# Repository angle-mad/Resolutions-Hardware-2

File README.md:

# Sasuke Bistable Multivibrator

This PCB is a Bistable Multivibrator in the shape of Sasuke from the anime Naruto. The LEDs change sides once a push switch gets pressed. There are two push swithes and the LED changes to go to the side opposite to the pussh switch. The LEDs are supposed to represent Sasuke's sharingan eyes. I made this projet because I want to better my hardware skills and because Naruto is one of my favorite shows and it is interesting way to show a Multivibrator that works with the show. 

---
## Lapse

[Lapse Video](https://lapse.hackclub.com/timelapse/BlOlKrzwhdhR)

## Simulation

The Bistable Multivibrator has two stable states. The circuit can stay in one of the two positions. This changes when a push switch is pressed. The push switch that is under the LED that is on will switch the state and cause the opposite LED to turn on.

[Link to Demo](https://is.gd/yXgSkD)

---
## Schematic

## PCB

---

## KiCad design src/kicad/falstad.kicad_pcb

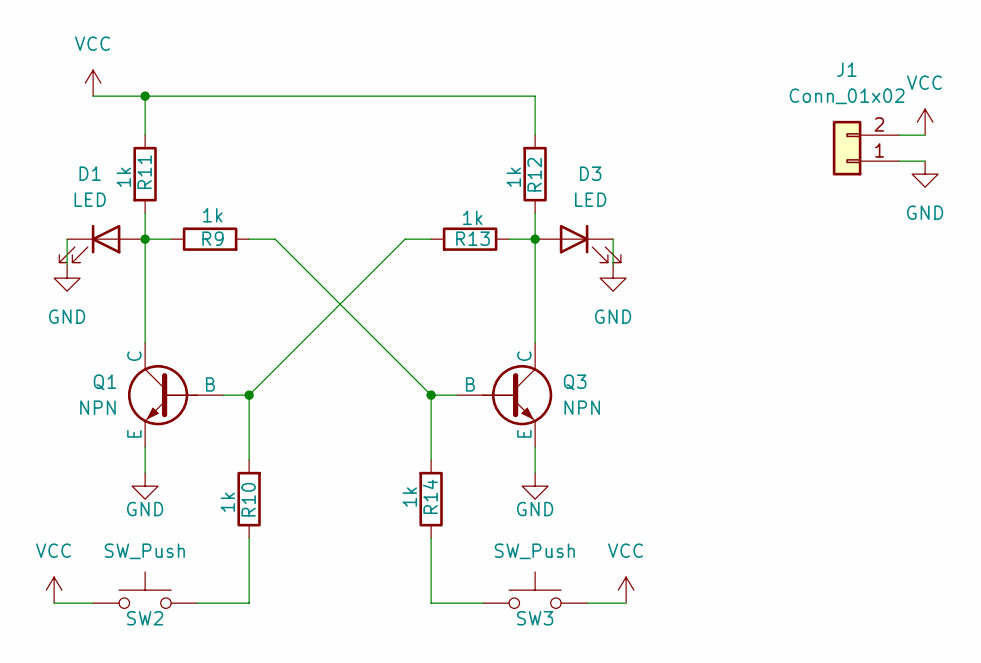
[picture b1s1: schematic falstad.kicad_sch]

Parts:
D1, D3: LED; LED_D5.0mm
J1: Conn_01x02; PinHeader_1x02_P2.54mm_Vertical
Q1, Q3: NPN; TO-92L_Inline_Wide
R9, R10, R11, R12, R13, R14: 1k; R_Axial_DIN0204_L3.6mm_D1.6mm_P7.62mm_Horizontal
SW2, SW3: SW_Push; SW_PUSH_6mm

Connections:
GND: D1.1 (K), D3.1 (K), J1.1, Q1.3 (E), Q3.3 (E)
unnamed: D1.2 (A), Q1.1 (C), R9.1, R11.2
unnamed: D3.2 (A), Q3.1 (C), R12.1, R13.1
unnamed: Q1.2 (B), R10.2, R13.2
unnamed: Q3.2 (B), R9.2, R14.2
unnamed: R10.1, SW2.2
unnamed: R14.1, SW3.2
VCC: J1.2, R11.1, R12.2, SW2.1, SW3.1

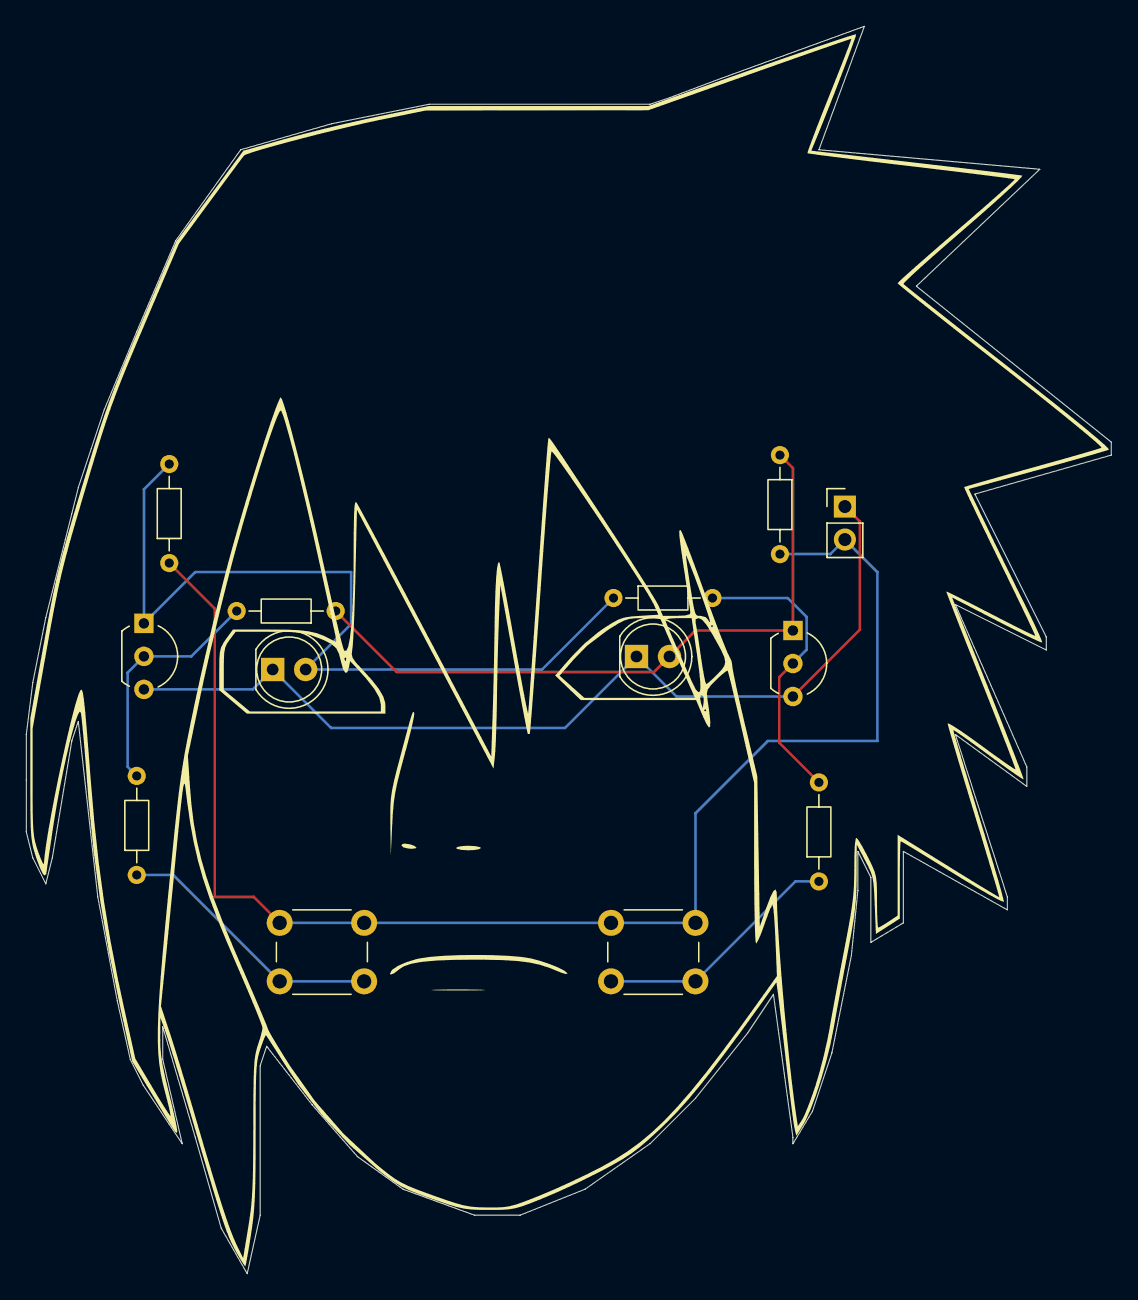
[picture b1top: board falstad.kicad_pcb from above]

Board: 2 copper layers, 83.5 x 96.0 mm, 13 parts (0 on the bottom side), 8 nets.

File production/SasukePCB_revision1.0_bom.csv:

Designator,Footprint,Quantity,Value,LCSC Part #
"D1, D3",LED_D5.0mm,2,LED,
J1,PinHeader_1x02_P2.54mm_Vertical,1,Conn_01x02,
"Q1, Q3",TO-92L_Inline_Wide,2,NPN,
"R10, R11, R12, R13, R14, R9",R_Axial_DIN0204_L3.6mm_D1.6mm_P7.62mm_Horizontal,6,1k,
"SW2, SW3",SW_PUSH_6mm,2,SW_Push,

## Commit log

2026-03-26 Update README with project details and images
    Added project title, images, and sections for simulation, schematic, and PCB.
2026-03-26 Create attachments
2026-03-26 Create temp
2026-03-26 Create temmp
2026-03-26 Create temm
2026-03-26 Fix demo link and update PCB image
    Updated demo link and replaced PCB image.
2026-03-26 Rename Screenshot 2026-03-26 045545.png to PCB_image
2026-03-26 Fix image paths and update project title
    Updated image paths and project title in README.
